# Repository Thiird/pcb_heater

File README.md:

# PCB Heater

As part of my journey in embedded systems I try to learn new technologies with projects that fix inconveniences in my life. One such inconvenience is that during the winter time, especially in the evening, during long computer-session my feet get terribly cold. So cold that when I finally decide to get up they hurt during the first steps.

To fix this I decided to create a small assembly that houses a plate capable of heating up to a set temperature, on which I can comfortably rest my feet while I'm at my desk.

The assembly consists of three main parts, the heating element, a driver circuit and the wood structure on which everything mounts on.

# Hardware

The heating element is 30x30 cm^2 pcb that features a long copper track that acts as a resistor, and thus heats up when current flows through it.

The pcb is made of three 10x30 cm^2 aluminum pcb connected in series. The reason for using three smaller pcbs instead of a big one, given that the minimum order is 5 units, is that the cost of making five 10x30 cm^2 pcbs is way less than making 5 30x30 cm^2 pcbs. Each single pcb has a resistance of 2 Ohms and has a track 2.64 meters long.

The heating element is powered via a MOSFET used as switch with PWM by an ESP32-S2-MINI-2 MCU. The driver board has an OLED screen and some tactile buttons to let the user set the target temperature and monitor the whole assembly.

The main power source is a 12V-80W AC/DC brick, which feeds the heating PCB and the MCU part of the circuit via a 3.3V switching regulator.

Check bom file for full parts list.

The driver PCB is enclosed in a 3D printed case, which is screwed on the wood assembly.

# Firmware

The firmware for the ESP32 is written with the ESP-IDF framework and runs FreeRTOS.

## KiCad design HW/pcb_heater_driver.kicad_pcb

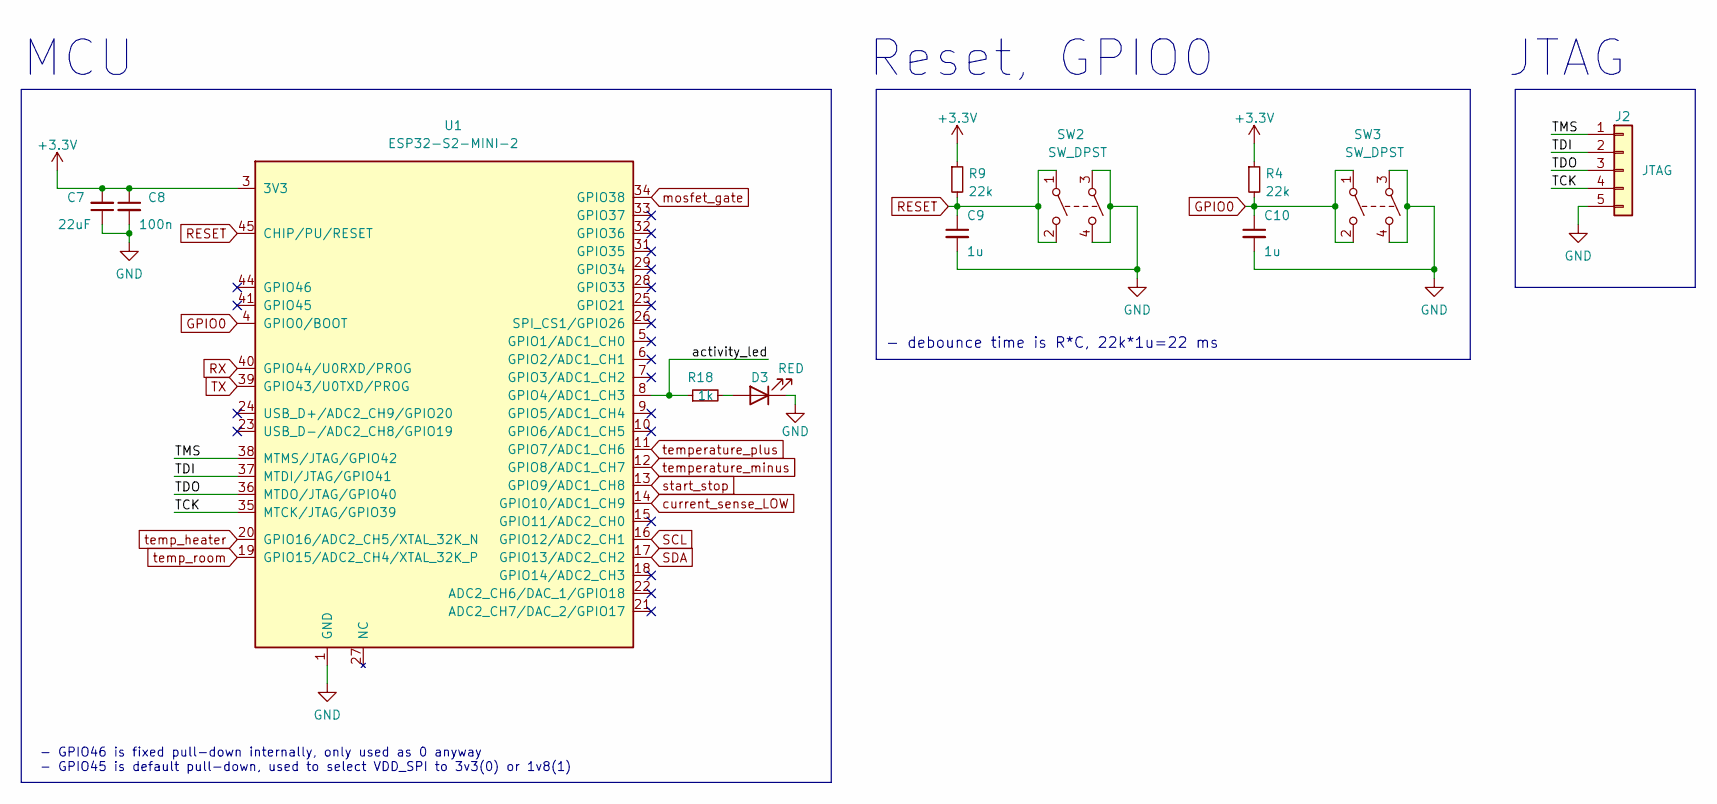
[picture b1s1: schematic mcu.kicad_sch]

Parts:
C7: 22uF; C_0603_1608Metric
C8: 100n; C_0603_1608Metric
C9, C10: 1u; C_0603_1608Metric
D3: RED; LED_0603_1608Metric
J2: JTAG; PinHeader_1x05_P2.54mm_Vertical
R4, R9: 22k; R_0603_1608Metric
R18: 1k; R_0603_1608Metric
SW2, SW3: SW_DPST; SW_SKRPACE010
U1: ESP32-S2-MINI-2; ESP32-S2-MINI-1

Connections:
/MCU/TCK: J2.4, U1.35 (MTCK/JTAG/GPIO39)
/MCU/TDI: J2.2, U1.37 (MTDI/JTAG/GPIO41)
/MCU/TDO: J2.3, U1.36 (MTDO/JTAG/GPIO40)
/MCU/TMS: J2.1, U1.38 (MTMS/JTAG/GPIO42)
/MCU/activity_led: R18.1, U1.8 (GPIO4/ADC1_CH3)
GND: C7.1, C8.2, C9.2, C10.2, D3.1 (K), J2.5, SW2.3, SW2.4, SW3.3, SW3.4, U1.1 (GND), U1.2 (GND), U1.30 (GND), U1.42 (GND), U1.43 (GND), U1.46 (GND), U1.47 (GND), U1.48 (GND), U1.49 (GND), U1.50 (GND), U1.51 (GND), U1.52 (GND), U1.53 (GND), U1.54 (GND), U1.55 (GND), U1.56 (GND), U1.57 (GND), U1.58 (GND), U1.59 (GND), U1.60 (GND), U1.61 (GND), U1.62 (GND), U1.63 (GND), U1.64 (GND), U1.65 (GND); also elsewhere on the board
GPIO0: C10.1, R4.2, SW3.1, SW3.2, U1.4 (GPIO0/BOOT); also elsewhere on the board
unnamed: D3.2 (A), R18.2
RESET: C9.1, R9.2, SW2.1, SW2.2, U1.45 (CHIP/PU/RESET); also elsewhere on the board
RX: U1.40 (GPIO44/U0RXD/PROG); also elsewhere on the board
SCL: U1.16 (GPIO12/ADC2_CH1); also elsewhere on the board
SDA: U1.17 (GPIO13/ADC2_CH2); also elsewhere on the board
TX: U1.39 (GPIO43/U0TXD/PROG); also elsewhere on the board
current_sense_LOW: U1.14 (GPIO10/ADC1_CH9); also elsewhere on the board
mosfet_gate: U1.34 (GPIO38); also elsewhere on the board
start_stop: U1.13 (GPIO9/ADC1_CH8); also elsewhere on the board
temp_heater: U1.20 (GPIO16/ADC2_CH5/XTAL_32K_N); also elsewhere on the board
temp_room: U1.19 (GPIO15/ADC2_CH4/XTAL_32K_P); also elsewhere on the board
temperature_minus: U1.12 (GPIO8/ADC1_CH7); also elsewhere on the board
temperature_plus: U1.11 (GPIO7/ADC1_CH6); also elsewhere on the board

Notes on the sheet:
Reset, GPIO0
JTAG
- debounce time is R*C, 22k*1u=22 ms
- GPIO46 is fixed pull-down internally, only used as 0 anyway - GPIO45 is default pull-down, used to select VDD_SPI to 3v3(0) or 1v8(1)
MCU

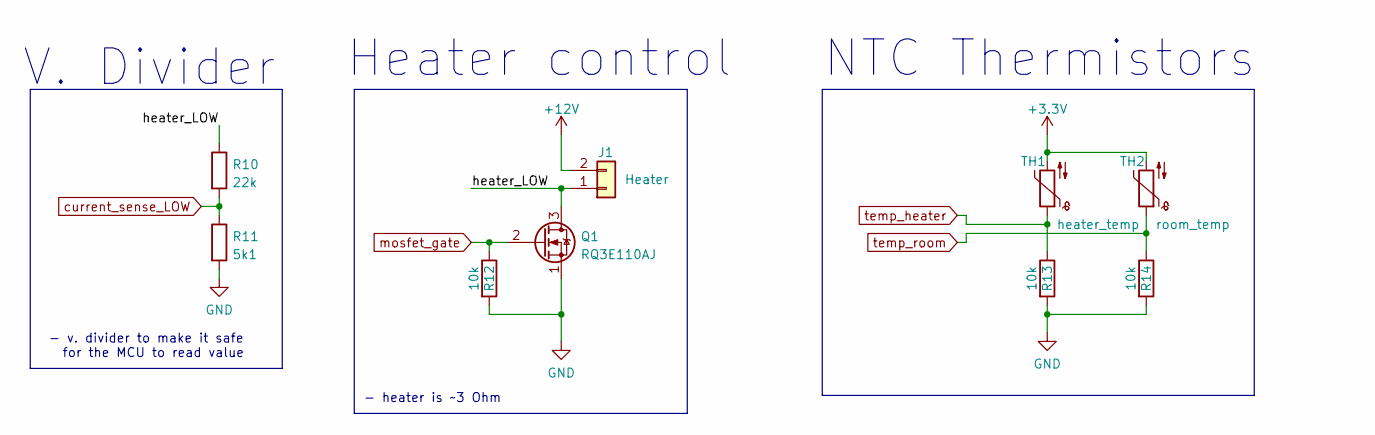
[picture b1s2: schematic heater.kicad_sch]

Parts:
J1: Heater; WR_TBL_Series_101
Q1: RQ3E110AJ; SOTFL65P330X80-8N
R10: 22k; R_0603_1608Metric
R11: 5k1; R_0603_1608Metric
R12, R13, R14: 10k; R_0603_1608Metric
TH1: heater_temp; SolderJumper-2_P1.3mm_Open_RoundedPad1.0x1.5mm
TH2: room_temp; SolderJumper-2_P1.3mm_Open_RoundedPad1.0x1.5mm

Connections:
+12V: J1.2; also elsewhere on the board
/Heater/heater_LOW: J1.1, Q1.3 (D), R10.1
GND: Q1.1 (S), R11.2, R12.2, R13.2, R14.2; also elsewhere on the board
current_sense_LOW: R10.2, R11.1; also elsewhere on the board
mosfet_gate: Q1.2 (G), R12.1; also elsewhere on the board
temp_heater: R13.1, TH1.1; also elsewhere on the board
temp_room: R14.1, TH2.1; also elsewhere on the board

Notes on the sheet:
V. Divider
NTC Thermistors
- heater is ~3 Ohm
- v. divider to make it safe for the MCU to read value
Heater control

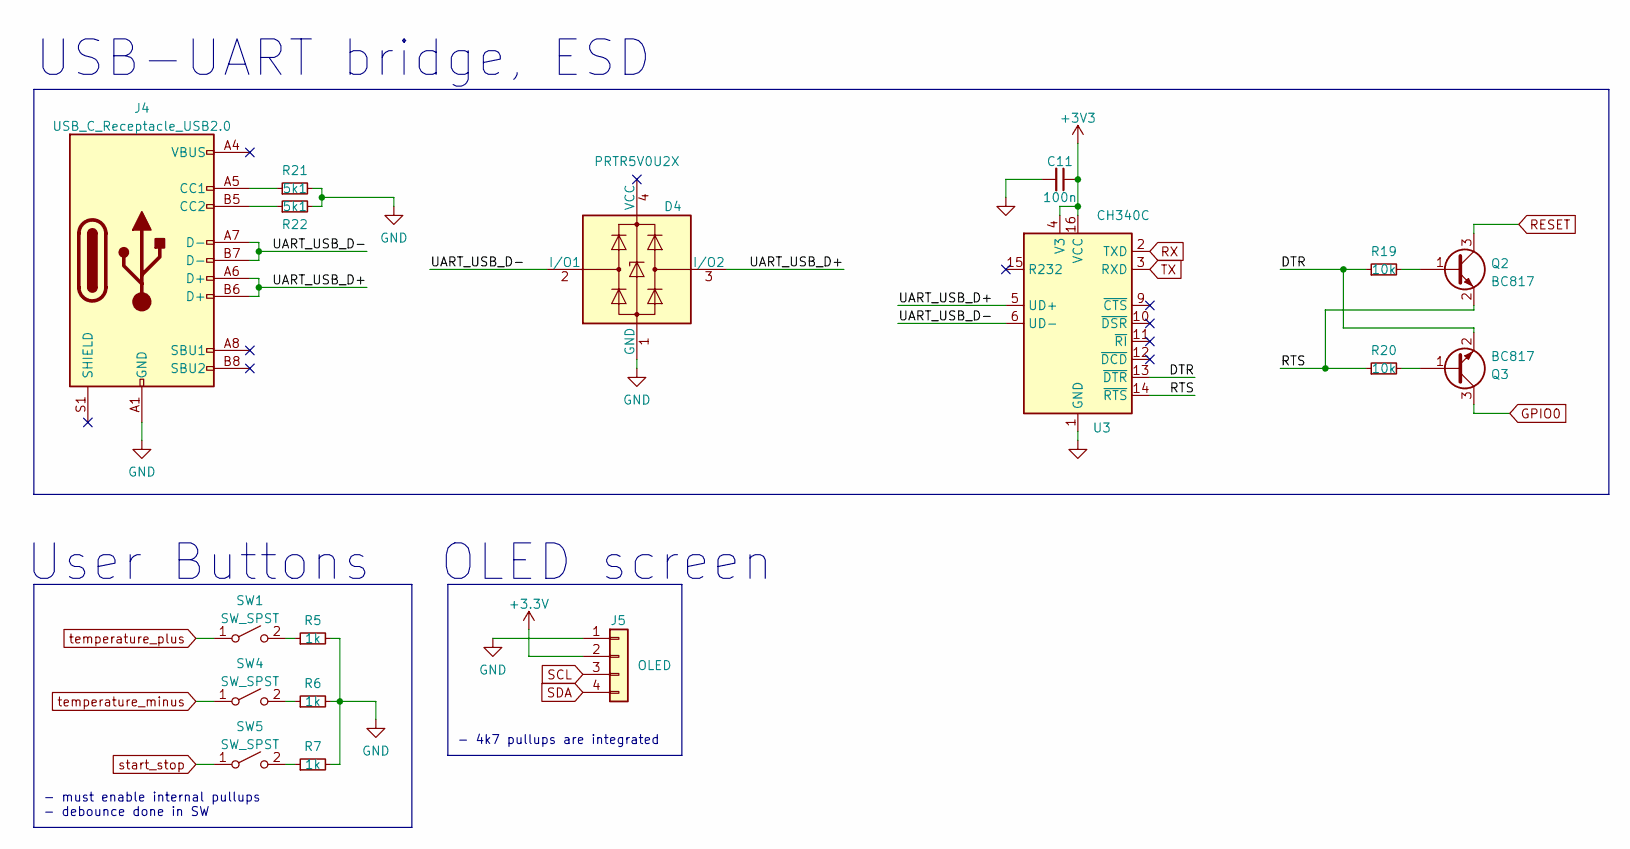
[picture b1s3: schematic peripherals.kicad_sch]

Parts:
C11: 100n; C_0603_1608Metric
D4: PRTR5V0U2X; SOT-143
J4: USB_C_Receptacle_USB2.0; USB_C_Receptacle_HRO_TYPE-C-31-M-12
J5: OLED; oled_angled
Q2, Q3: BC817; SOT-23
R5, R6, R7: 1k; R_0603_1608Metric
R19, R20: 10k; R_0603_1608Metric
R21, R22: 5k1; R_0603_1608Metric
SW1, SW4, SW5: SW_SPST; SW_1-1825027-1
U3: CH340C; SOIC-16_3.9x9.9mm_P1.27mm

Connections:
/Peripherals/DTR: Q3.2 (E), R19.1, U3.13 (~DTR)
/Peripherals/RTS: Q2.2 (E), R20.1, U3.14 (~RTS)
/Peripherals/UART_USB_D+: D4.3 (I/O2), J4.A6 (D+), J4.B6 (D+), U3.5 (UD+)
/Peripherals/UART_USB_D-: D4.2 (I/O1), J4.A7 (D-), J4.B7 (D-), U3.6 (UD-)
GND: C11.2, D4.1 (GND), J4.A1 (GND), J4.A12 (GND), J4.B1 (GND), J4.B12 (GND), J5.1, R5.2, R6.2, R7.2, R21.2, R22.2, U3.1 (GND); also elsewhere on the board
GPIO0: Q3.3 (C); also elsewhere on the board
unnamed: J4.A5 (CC1), R21.1
unnamed: J4.B5 (CC2), R22.1
unnamed: Q2.1 (B), R19.2
unnamed: Q3.1 (B), R20.2
unnamed: R5.1, SW1.2 (B)
unnamed: R6.1, SW4.2 (B)
unnamed: R7.1, SW5.2 (B)
RESET: Q2.3 (C); also elsewhere on the board
RX: U3.2 (TXD); also elsewhere on the board
SCL: J5.3; also elsewhere on the board
SDA: J5.4; also elsewhere on the board
TX: U3.3 (RXD); also elsewhere on the board
start_stop: SW5.1 (A); also elsewhere on the board
temperature_minus: SW4.1 (A); also elsewhere on the board
temperature_plus: SW1.1 (A); also elsewhere on the board

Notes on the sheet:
- 4k7 pullups are integrated
User Buttons
OLED screen
USB-UART bridge, ESD
- must enable internal pullups - debounce done in SW

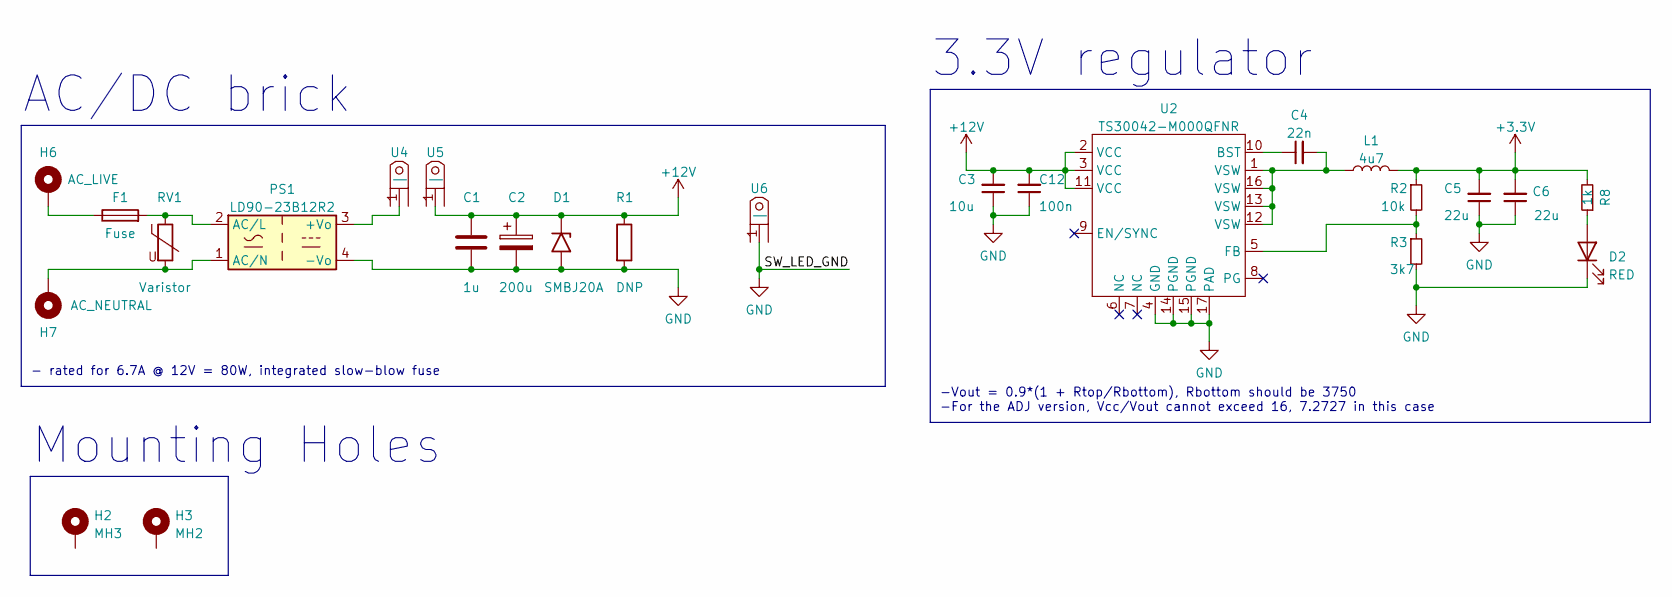
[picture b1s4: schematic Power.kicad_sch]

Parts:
C1: 1u; C_1206_3216Metric; rating 100V
C2: 200u; CP_Radial_D10.0mm_P5.00mm; rating 35V
C3: 10u; C_0603_1608Metric; rating 50V
C4: 22n; C_0603_1608Metric
C5, C6: 22u; C_0603_1608Metric
C12: 100n; C_0603_1608Metric; rating 50V
D1: SMBJ20A; D_SMB
D2: RED; LED_0603_1608Metric
F1: Fuse; 3622
H2: MH3; MountingHole_3.2mm_M3_Pad_TopBottom
H3: MH2; MountingHole_3.2mm_M3_Pad_TopBottom
H6: AC_LIVE; MountingHole_2.2mm_M2_Pad_TopBottom
H7: AC_NEUTRAL; MountingHole_2.2mm_M2_Pad_TopBottom
L1: 4u7; BWVS005050404R7M00
PS1: LD90-23B12R2
R1: DNP; R_2010_5025Metric
R2: 10k; R_0603_1608Metric
R3: 3k7; R_0603_1608Metric
R8: 1k; R_0603_1608Metric
RV1: Varistor; B72214S0351K101
U2: TS30042-M000QFNR; QFN-16-1EP_3x3mm_P0.5mm_EP1.75x1.75mm_ThermalVias
U4, U5, U6: fork_p5.0mm

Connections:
+12V: C1.1, C2.1, C3.2, C12.2, D1.1 (A1), R1.1, U2.2 (VCC), U2.3 (VCC), U2.11 (VCC), U5.1 (|); also elsewhere on the board
GND: C1.2, C2.2, C3.1, C5.1, C6.1, C12.1, D1.2 (A2), D2.1 (K), PS1.4 (-Vo), R1.2, R3.2, U2.4 (GND), U2.14 (PGND), U2.15 (PGND), U2.17 (PAD), U6.1 (|); also elsewhere on the board
unnamed: C4.1, U2.10 (BST)
unnamed: C4.2, L1.1, U2.1 (VSW), U2.12 (VSW), U2.13 (VSW), U2.16 (VSW)
unnamed: D2.2 (A), R8.1
unnamed: F1.1, H6.1
unnamed: F1.2, PS1.2 (AC/L), RV1.1
unnamed: H7.1, PS1.1 (AC/N), RV1.2
unnamed: PS1.3 (+Vo), U4.1 (|)
unnamed: R2.2, R3.1, U2.5 (FB)

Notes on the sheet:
AC/DC brick
Mounting Holes
- rated for 6.7A @ 12V = 80W, integrated slow-blow fuse
-Vout = 0.9*(1 + Rtop/Rbottom), Rbottom should be 3750 -For the ADJ version, Vcc/Vout cannot exceed 16, 7.2727 in this case
3.3V regulator

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
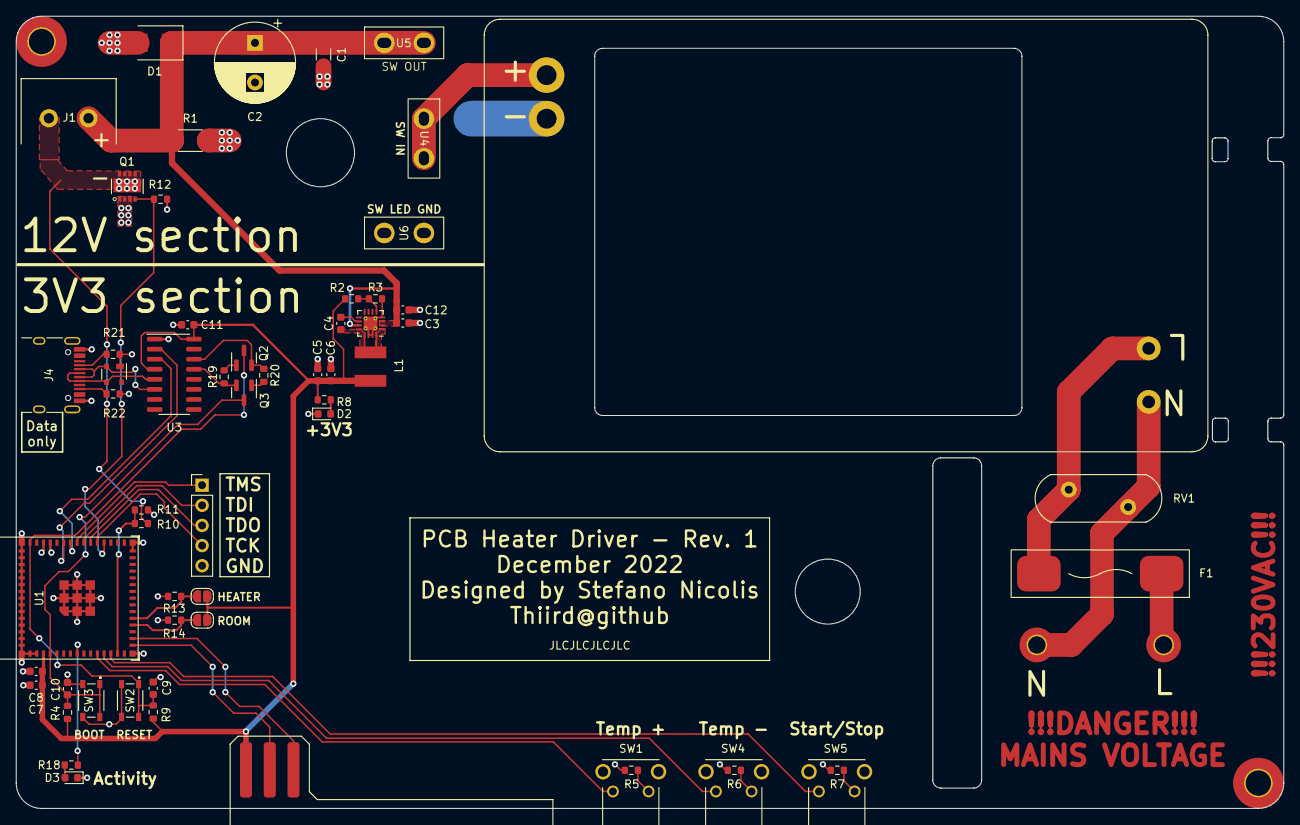
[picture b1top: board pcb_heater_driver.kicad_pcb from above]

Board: 2 copper layers, 160.0 x 100.0 mm, 63 parts (0 on the bottom side), 42 nets.

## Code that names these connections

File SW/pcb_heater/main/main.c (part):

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#include "ssd1306.h"
#include "math.h"

#define ACTIVITY_LED GPIO_NUM_4        // GPIO4, activity led, active high
#define TEMP_INC_BTN GPIO_NUM_7        // GPIO7, increase target temperature, active low
#define TEMP_DEC_BTN GPIO_NUM_8        // GPIO8, decrease target temperature, active low
#define START_STOP_BTN GPIO_NUM_9      // GPIO9, start/stop heating, active low
#define HEATER_MOSFET_GATE GPIO_NUM_38 // GPIO38
#define MAX_ALLOWED_TEMP 55            // °C
#define ADC_RESOLUTION ADC_BITWIDTH_13
#define ADC_MAX_VALUE 8191.0
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#define LEDC_DUTY_RES_ACTUAL 8192 // 2 ^ 13
#define LEDC_FREQ 1000            // 1KHz

#define I2C_SDA 13           // GPIO13
#define I2C_SCL 12           // GPIO12
#define I2C_FREQUENCY 100000 // 100 Kb/s
#define I2C_USED_PORT I2C_NUM_0

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    gpio_config_t io_conf = {
        io_conf.intr_type = GPIO_INTR_DISABLE,       // disable interrupt
        io_conf.mode = GPIO_MODE_OUTPUT,             // set as output mode
        io_conf.pin_bit_mask = 1ULL << ACTIVITY_LED, // bit mask of the pins that you want to set
        io_conf.pull_down_en = 0,                    // disable pull-down mode
        io_conf.pull_up_en = 0};                     // disable pull-up mode
    ESP_ERROR_CHECK(gpio_config(&io_conf));
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        .rx_flow_ctrl_thresh = 122};
    ESP_ERROR_CHECK(uart_param_config(uart_num, &uart_config));

    // Set UART pins(TX: IO39, RX: IO44, RTS: IO5, CTS: IO6), RTS and CTS not used
    ESP_ERROR_CHECK(uart_set_pin(UART_NUM_0, 39, 44, 5, 6));

    // Setup UART buffered IO with event queue
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{
    while (true)
    {
        gpio_set_level(ACTIVITY_LED, 1);
        vTaskDelay(ONE_SECOND);
        gpio_set_level(ACTIVITY_LED, 0);
        vTaskDelay(ONE_SECOND);
    }
}
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
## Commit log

2022-11-12 Initial commit, will I do this?
2022-11-13 Lots of progress on heater PCB and links
2022-11-13 Progress
2022-11-14 Sectioned schematic, reqorked heater trace length and thickness
2022-11-15 Fixed board, big work in schematic, to finish
2022-11-16 Finished sch, to be checked. Initial components layout
2022-11-16 Sch finalized, added EMC stuff, user buttons and oled
2022-11-18 Work on layout, sch fixes, added several 3d models
2022-11-18 Removed heavy file
2022-11-18 starterd routing, removed OTG usb port
2022-11-19 Finished routing, only mosfet left, fixed layout, outline
2022-11-20 Fix board, QOL fixes
2022-11-24 QOL changes on pcb, fixed wrong ACDC brick polarity xD
2022-11-25 revision 0
2022-12-03 Firmware start, learning ESP-IDF
2022-12-04 Added uart and gpio init, basic main
2022-12-04 Addede ISRs for user buttons, functions templates
2022-12-06 Added ADCs init, added some variables
2022-12-08 Readme work
2022-12-08 Readme and board fixes
2022-12-09 Added i2c init and write
2022-12-10 Started SSD1306 oled driver
2022-12-10 i2c and ssd1306 refactor
2022-12-10 More ssd1306 work, implemented pwm for mosfet driving
2022-12-11 Found ssd1306 library, using that to speedup dev :(
2022-12-15 First flash, code tidy up, buttons debounce, oled test
2022-12-15 Fixed silkscreen, removed one thermistor, fixed component placement
2022-12-15 Fixed buttons debounce, fixed i2c
2022-12-16 Fixed adc, fixed pwm, first test run succesful!
2022-12-16 Fixed component placement, enlarged some pcb slots, removed two thermistors
2022-12-17 Fixed NTC implementation
